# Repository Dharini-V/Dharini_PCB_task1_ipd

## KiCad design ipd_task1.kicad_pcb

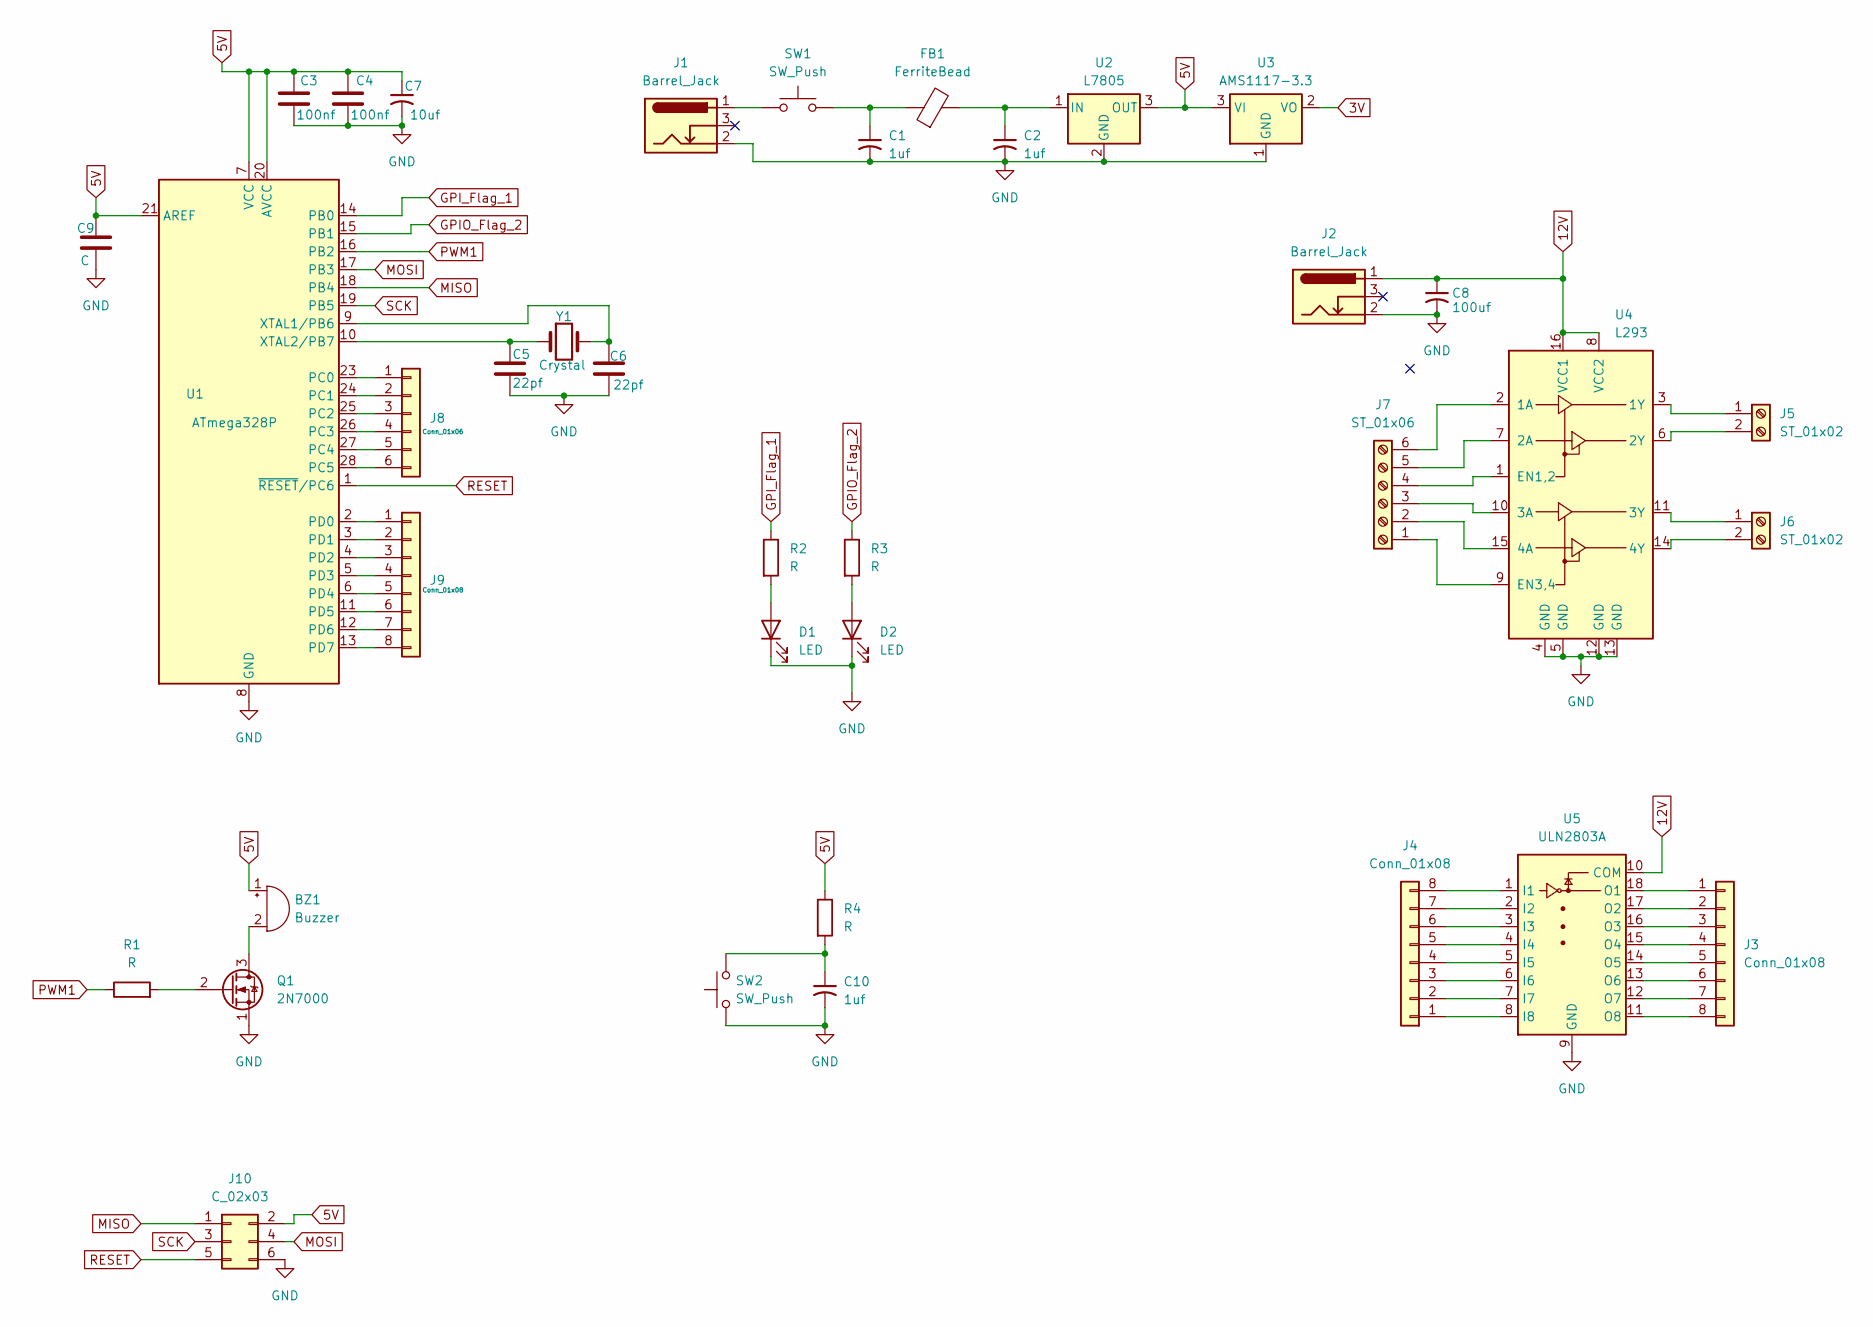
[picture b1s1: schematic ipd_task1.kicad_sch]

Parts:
BZ1: Buzzer; Buzzer_12x9.5RM7.6
C1, C2, C10: 1uf; C_Radial_D5.0mm_H5.0mm_P2.00mm
C3, C4: 100nf; C_Disc_D5.0mm_W2.5mm_P2.50mm
C5, C6: 22pf; C_Disc_D5.0mm_W2.5mm_P2.50mm
C7: 10uf; C_Radial_D5.0mm_H5.0mm_P2.00mm
C8: 100uf; C_Radial_D5.0mm_H5.0mm_P2.00mm
C9: C; C_Disc_D5.0mm_W2.5mm_P2.50mm
D1, D2: LED; LED_D5.0mm
FB1: FerriteBead; L_Axial_L7.0mm_D3.3mm_P10.16mm_Horizontal_Fastron_MICC
J1, J2: Barrel_Jack; BarrelJack_CUI_PJ-063AH_Horizontal
J3, J4, J9: Conn_01x08; PinHeader_1x08_P2.54mm_Vertical
J5, J6: ST_01x02; TerminalBlock_Phoenix_MKDS-1,5-2-5.08_1x02_P5.08mm_Horizont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
J7: ST_01x06; TerminalBlock_Phoenix_MKDS-1,5-6-5.08_1x06_P5.08mm_Horizont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
J8: Conn_01x06; PinHeader_1x06_P2.54mm_Vertical
J10: C_02x03; PinSocket_2x03_P2.54mm_Vertical
Q1: 2N7000; TO-92_Inline
R1, R2, R3, R4: R; R_Axial_DIN0207_L6.3mm_D2.5mm_P7.62mm_Horizontal
SW1, SW2: SW_Push; SW_PUSH_6mm
U1: ATmega328P; DIP-28_W7.62mm
U2: L7805; TO-220-3_Vertical
U3: AMS1117-3.3; SOT-223-3_TabPin2
U4: L293; DIP-16_W7.62mm
U5: ULN2803A; DIP-18_W7.62mm
Y1: Crystal; Crystal_HC49-U_Vertical

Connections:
3V: U3.2 (VO)
5V: BZ1.1 (+), C3.1, C4.1, C7.1, C9.1, J10.2, R4.1, U1.7 (VCC), U1.20 (AVCC), U1.21 (AREF), U2.3 (OUT), U3.3 (VI)
12V: C8.1, J2.1, U4.8 (VCC2), U4.16 (VCC1), U5.10 (COM)
GND: C1.2, C2.2, C3.2, C4.2, C5.2, C6.2, C7.2, C8.2, C9.2, C10.2, D1.1 (K), D2.1 (K), J1.2, J2.2, J10.6, Q1.1 (S), SW2.1, U1.8 (GND), U1.22 (GND), U2.2 (GND), U3.1 (GND), U4.4 (GND), U4.5 (GND), U4.12 (GND), U4.13 (GND), U5.9 (GND)
GPIO_Flag_2: R3.1, U1.15 (PB1)
GPI_Flag_1: R2.1, U1.14 (PB0)
MISO: J10.1, U1.18 (PB4)
MOSI: J10.4, U1.17 (PB3)
unnamed: BZ1.2 (-), Q1.3 (D)
unnamed: C1.1, FB1.1, SW1.2
unnamed: C10.1, R4.2, SW2.2
unnamed: D1.2 (A), R2.2
unnamed: D2.2 (A), R3.2
unnamed: J1.1, SW1.1
unnamed: J3.1, U5.18 (O1)
unnamed: J3.2, U5.17 (O2)
unnamed: J3.3, U5.16 (O3)
unnamed: J3.4, U5.15 (O4)
unnamed: J3.5, U5.14 (O5)
unnamed: J3.6, U5.13 (O6)
unnamed: J3.7, U5.12 (O7)
unnamed: J3.8, U5.11 (O8)
unnamed: J4.1, U5.8 (I8)
unnamed: J4.2, U5.7 (I7)
unnamed: J4.3, U5.6 (I6)
unnamed: J4.4, U5.5 (I5)
unnamed: J4.5, U5.4 (I4)
unnamed: J4.6, U5.3 (I3)
unnamed: J4.7, U5.2 (I2)
unnamed: J4.8, U5.1 (I1)
unnamed: J5.1, U4.3 (1Y)
unnamed: J5.2, U4.6 (2Y)
unnamed: J6.1, U4.11 (3Y)
unnamed: J6.2, U4.14 (4Y)
unnamed: J7.1, U4.9 (EN3,4)
unnamed: J7.2, U4.15 (4A)
unnamed: J7.3, U4.10 (3A)
unnamed: J7.4, U4.1 (EN1,2)
unnamed: J7.5, U4.7 (2A)
unnamed: J7.6, U4.2 (1A)
unnamed: J8.1, U1.23 (PC0)
unnamed: J8.2, U1.24 (PC1)
unnamed: J8.3, U1.25 (PC2)
unnamed: J8.4, U1.26 (PC3)
unnamed: J8.5, U1.27 (PC4)
unnamed: J8.6, U1.28 (PC5)
unnamed: J9.1, U1.2 (PD0)
unnamed: J9.2, U1.3 (PD1)
unnamed: J9.3, U1.4 (PD2)
unnamed: J9.4, U1.5 (PD3)
unnamed: J9.5, U1.6 (PD4)
unnamed: J9.6, U1.11 (PD5)
unnamed: J9.7, U1.12 (PD6)
unnamed: J9.8, U1.13 (PD7)
unnamed: Q1.2 (G), R1.2
unnamed: C6.1, U1.9 (XTAL1/PB6), Y1.2
unnamed: C5.1, U1.10 (XTAL2/PB7), Y1.1
unnamed: C2.1, FB1.2, U2.1 (IN)
PWM1: R1.1, U1.16 (PB2)
RESET: J10.5, U1.1 (~RESET/PC6)
SCK: J10.3, U1.19 (PB5)

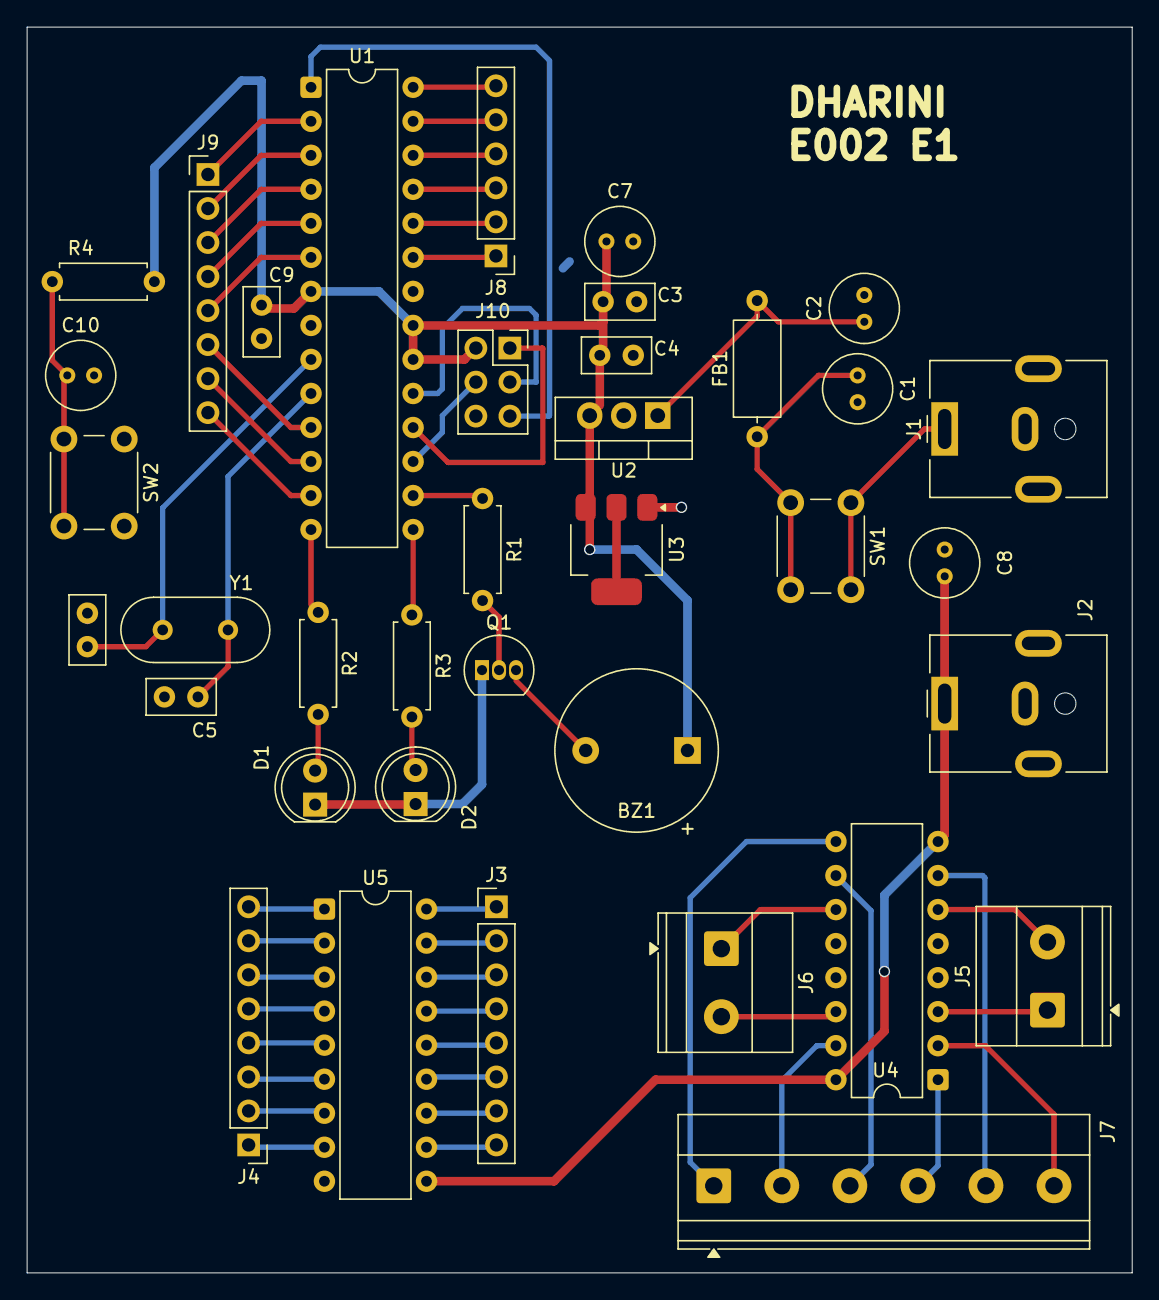
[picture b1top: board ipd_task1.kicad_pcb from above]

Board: 2 copper layers, 82.5 x 93.0 mm, 37 parts (0 on the bottom side), 60 nets.
